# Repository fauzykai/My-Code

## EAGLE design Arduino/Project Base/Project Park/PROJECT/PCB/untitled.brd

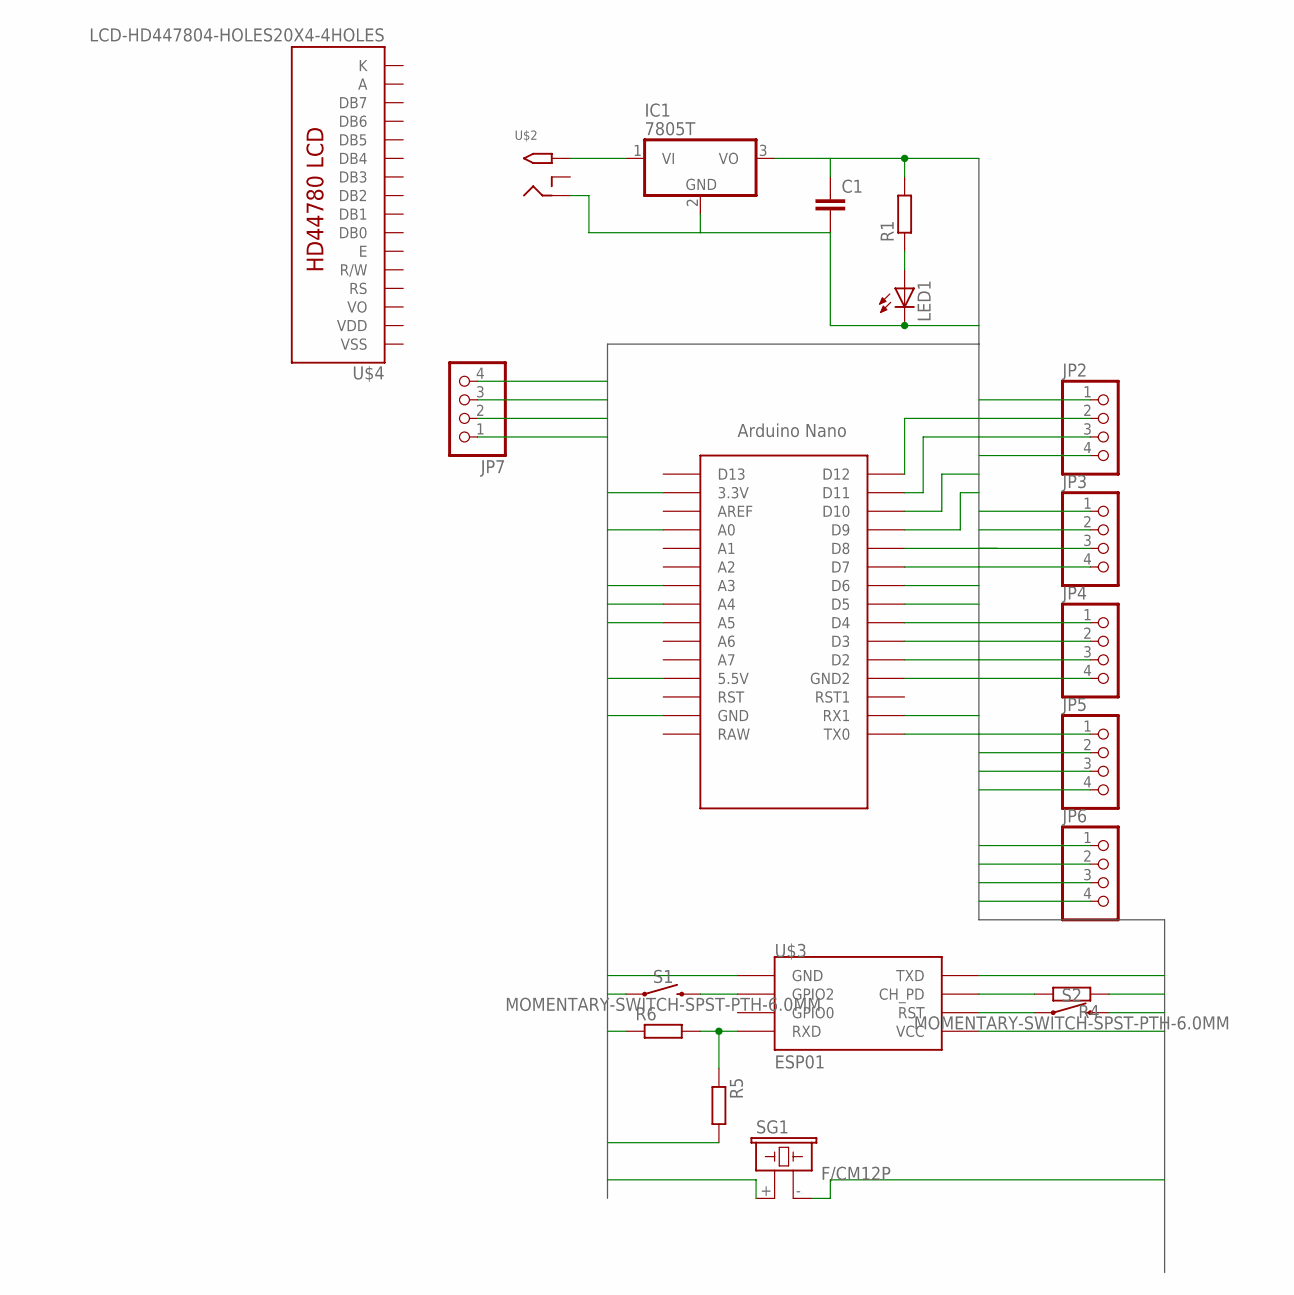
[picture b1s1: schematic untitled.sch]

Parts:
C1: C-EU025-030X050; C025-030X050
IC1: 7805T; TO220H
JP2, JP3, JP4, JP5, JP6, JP7: PINHD-1X4; 1X04
LED1: LED5MM
R1, R4, R5, R6: R-EU_0204/7; 0204/7
S1, S2: MOMENTARY-SWITCH-SPST-PTH-6.0MM; TACTILE_SWITCH_PTH_6.0MM
SG1: F/CM12P
U$1: NANO
U$2: 2.1MMJACKTHM; PJ-102A
U$3: ESP01
U$4: LCD-HD447804-HOLES20X4-4HOLES; LCD-20X4-4HOLES

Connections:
3V: R4.1, U$1.3.3V, U$3.VCC
A: U$4.P$15 (A)
BUZZ: SG1.+ (1), U$1.A3
E1: JP2.3, U$1.D11
E2: JP3.3, U$1.D9
E3: JP4.3, U$1.D7
E4: JP5.3, U$1.D5
E5: JP6.3, U$1.A0
GND: C1.2, IC1.2 (GND), JP2.4, JP3.4, JP4.4, JP5.4, JP6.4, JP7.1, LED1.K (C), R5.2, S1.1, S2.3 (2), SG1.- (2), U$1.GND, U$1.GND1 (GND2), U$2.RING, U$3.GND
K: U$4.P$16 (K)
unnamed: IC1.1 (VI), U$2.TIP
unnamed: R4.2, U$3.CH_PD
unnamed: R5.1, R6.2, U$3.RX (RXD)
unnamed: LED1.A, R1.1
unnamed: S1.3 (2), U$3.GPIO2
unnamed: S2.1, U$3.RST
RX: U$1.RX1
RXS: U$1.D3, U$3.TX (TXD)
SCL: JP7.3, U$1.A5
SDA: JP7.2, U$1.A4
T1: JP2.2, U$1.D12
T2: JP3.2, U$1.D10
T3: JP4.2, U$1.D8
T4: JP5.2, U$1.D6
T5: JP6.2, U$1.D4
TX: U$1.TX0
TXS: R6.1, U$1.D2
VCC: C1.1, IC1.3 (VO), JP2.1, JP3.1, JP4.1, JP5.1, JP6.1, JP7.4, R1.2, U$1.5V (5.5V)
VDD: U$4.P$2 (VDD)
VSS: U$4.P$1 (VSS)

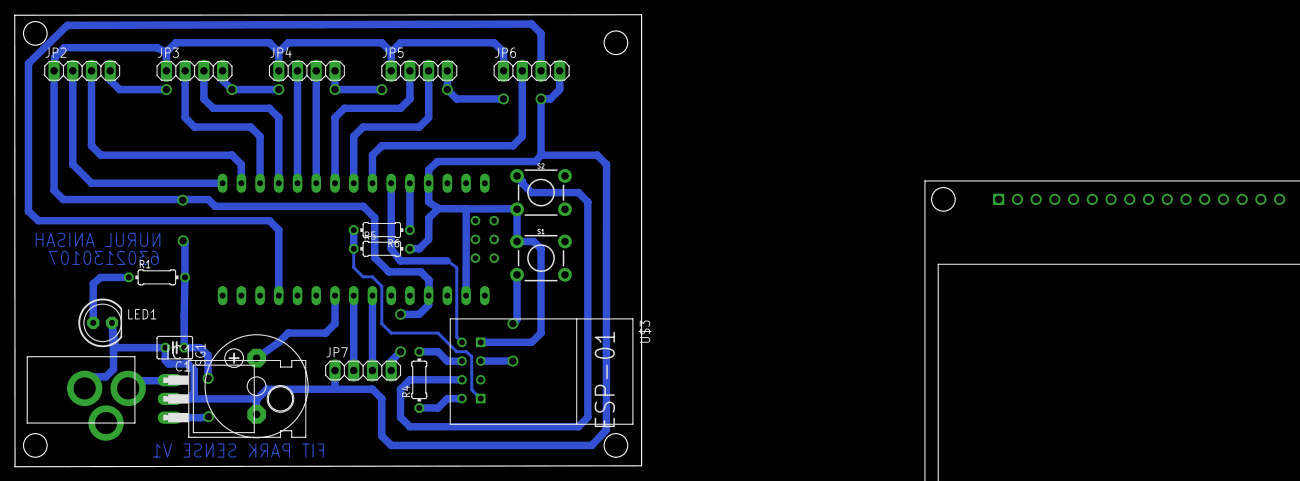
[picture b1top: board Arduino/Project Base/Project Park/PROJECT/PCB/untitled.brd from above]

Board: 2 copper layers, 85.0 x 61.3 mm, 20 parts (0 on the bottom side), 24 nets.

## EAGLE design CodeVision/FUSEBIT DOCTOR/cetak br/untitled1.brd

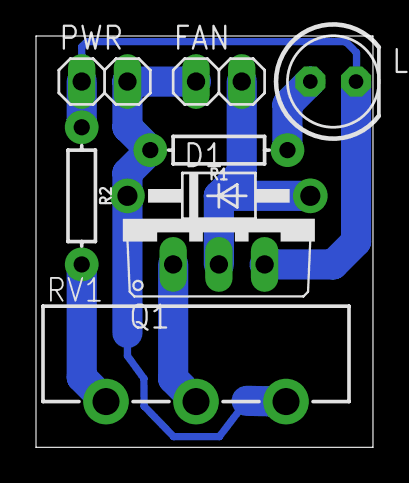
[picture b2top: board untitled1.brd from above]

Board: 2 copper layers, 18.7 x 22.9 mm, 8 parts (0 on the bottom side), 6 nets.

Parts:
D1: 1N4004; DO41-10
FAN: 1X02
LED1: LED5MM
PWR: 1X02
Q1: TO220V
R1, R2: 10M; AXIAL-0.3
RV1: POT_ALPHA_RV16AF-20

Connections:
GND: LED1.K, PWR.1, Q1.3, R2.P$1
unnamed: R2.P$2, RV1.1
unnamed: D1.A, FAN.2, Q1.2
unnamed: LED1.A, R1.P$1
unnamed: Q1.1, RV1.2
VCC: D1.C, FAN.1, PWR.2, R1.P$2, RV1.3

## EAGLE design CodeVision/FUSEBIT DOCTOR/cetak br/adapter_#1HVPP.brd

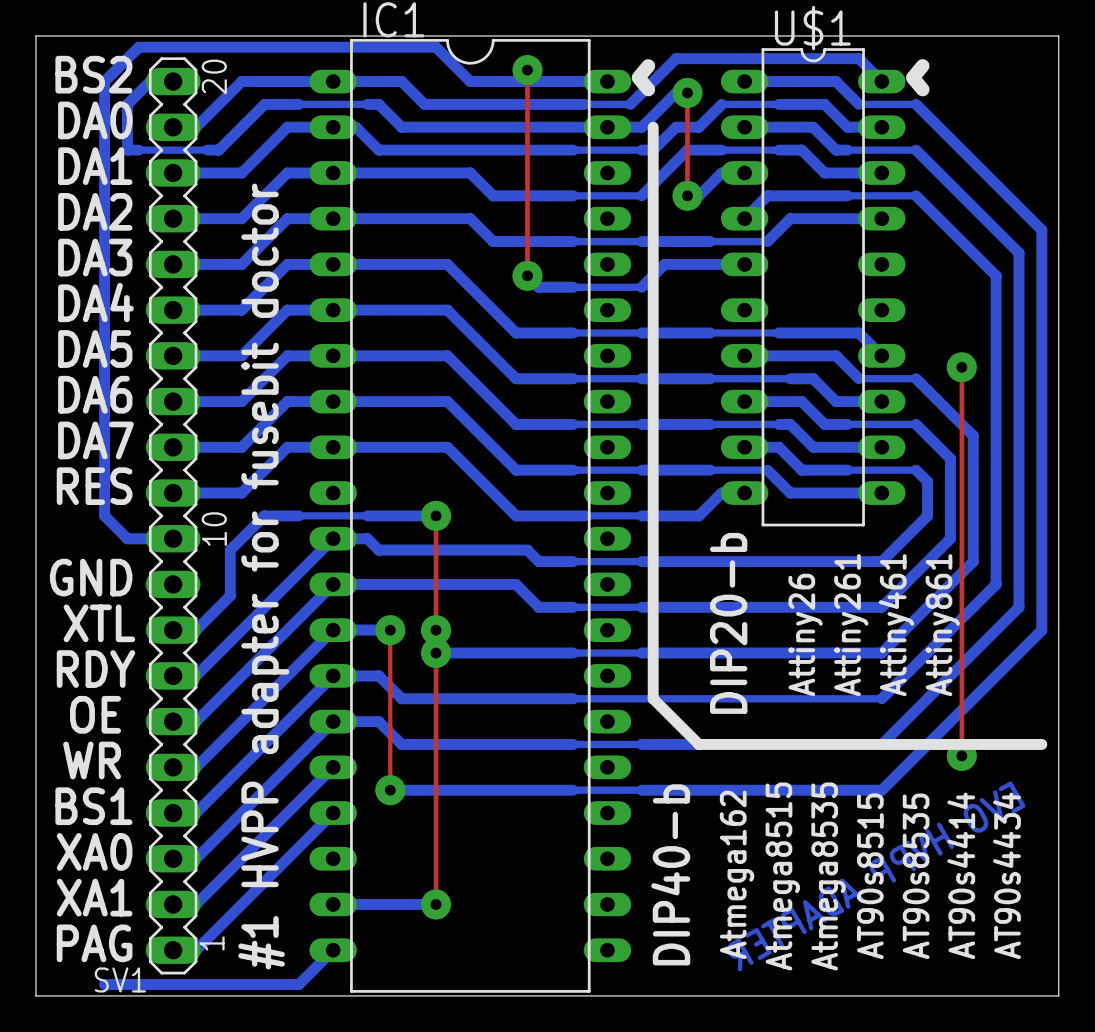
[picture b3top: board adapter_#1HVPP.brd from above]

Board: 2 copper layers, 56.8 x 53.3 mm, 3 parts (0 on the bottom side), 20 nets.

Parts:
IC1: AT90S8515P; DIL40
SV1: MA20-1
U$1: TINY26P; DIL20

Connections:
+5V: IC1.40, SV1.10, U$1.5
+12V: IC1.9, SV1.11, U$1.10
BS1: IC1.14, SV1.4, U$1.4
BS2: IC1.39, SV1.20, U$1.3
DATA0: IC1.1, SV1.19, U$1.20
DATA1: IC1.2, SV1.18, U$1.19
DATA2: IC1.3, SV1.17, U$1.18
DATA3: IC1.4, SV1.16, U$1.17
DATA4: IC1.5, SV1.15, U$1.14
DATA5: IC1.6, SV1.14, U$1.13
DATA6: IC1.7, SV1.13, U$1.12
DATA7: IC1.8, SV1.12, U$1.11
GND: IC1.20, SV1.9, U$1.16
OE: IC1.12, SV1.6, U$1.8
PAG: IC1.17, SV1.1
RDY: IC1.11, SV1.7, U$1.9
WR: IC1.13, SV1.5, U$1.1
XA0: IC1.15, SV1.3, U$1.2
XA1: IC1.16, SV1.2
XTAL1: IC1.19, SV1.8, U$1.7

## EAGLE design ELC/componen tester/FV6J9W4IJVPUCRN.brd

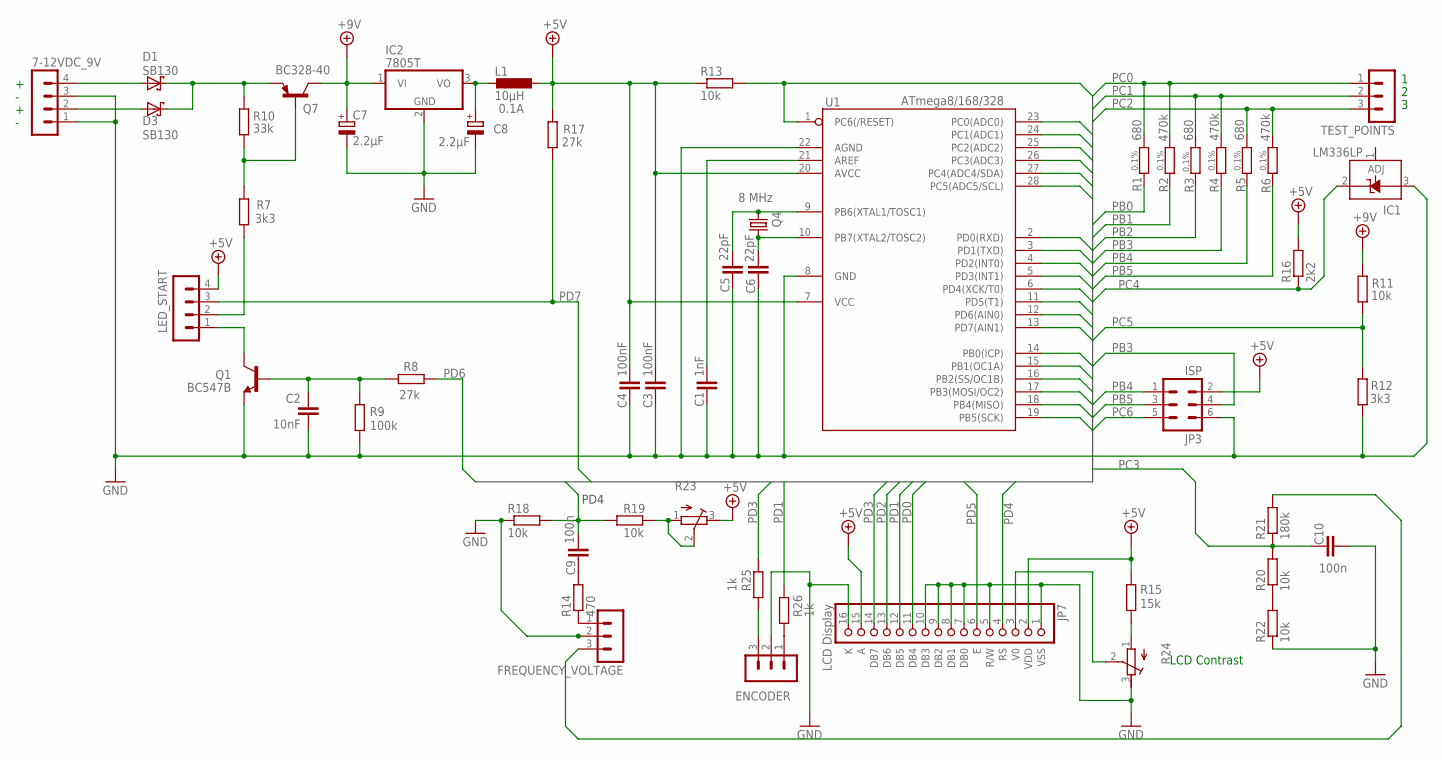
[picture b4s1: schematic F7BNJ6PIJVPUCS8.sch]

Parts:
7-12VDC_9V: MA04-1
C1: 1nF; C2.5-2
C2: 10nF; C2.5-3
C3, C4: 100nF; C025-025X050
C5, C6: 22pF; C2.5-3
C7, C8: 2.2µF; E5-5
C9, C10: 100n; C2.5-3
D1, D3: SB130; DIODE-3-5A-V
ENCODER: MA03-1
FREQUENCY_VOLTAGE: MA03-1
IC1: LM336LP; TO92
IC2: 7805T; TO220H
JP3: ISP; ML6
JP7: LCD Display; PINHD-1X16
L1: 10µH; 0204/7
LED_START: MA04-1
Q1: BC547B; TO92
Q4: 8 MHz; HC49/S
Q7: BC328-40; TO92-EBC
R1, R5: 680; 0207/10; TOLERANCE 0.1%
R2, R4, R6: 470k; 0207/10; TOLERANCE 0.1%
R3: 680; 0207/10; TOLERANCE 0,1%
R7: 3k3; 0207/10
R8: 27k; 0204/7
R9: 100k; 0204/7
R10: 33k; 0207/2V
R11, R13, R18, R19, R20, R22: 10k; 0207/10
R12: 3k3; 0207/2V
R14: 470; 0207/10
R15: 15k; 0207/10
R16: 2k2; 0204/5
R17: 27k; 0207/7
R21: 180k; 0207/10
R23, R24: R-TRIMM3339P; RTRIM3339P
R25: 1k; 0204/7
R26: 1k; 0207/10
TEST_POINTS: MA03-1
U1: ATmega8/168/328; DIL28-3

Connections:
+5V: C3.2, C4.1, JP3.2, JP7.2 (VDD), JP7.15 (A), L1.1, LED_START.4, R13.1, R15.1, R16.2, R17.2, R23.3 (E), U1.7 (VCC), U1.20 (AVCC)
+9V: C7.+, IC2.1 (VI), Q7.C, R11.1
GND: 7-12VDC_9V.1, 7-12VDC_9V.3, C1.1, C2.2, C3.1, C4.2, C5.1, C6.1, C7.-, C8.-, C10.1, ENCODER.2, FREQUENCY_VOLTAGE.2, IC1.3 (A), IC2.2 (GND), JP3.6, JP7.1 (VSS), JP7.5 (R/W), JP7.7 (DB0), JP7.8 (DB1), JP7.9 (DB2), JP7.10 (DB3), JP7.16 (K), Q1.1 (E), R9.1, R12.1, R18.1, R22.1, R24.3 (E), U1.8 (GND), U1.22 (AGND)
unnamed: R15.2, R24.1 (A)
unnamed: JP7.3 (V0), R24.2 (S)
unnamed: FREQUENCY_VOLTAGE.1, R14.1
unnamed: C9.1, R14.2
unnamed: D1.C, D3.C, Q7.E, R10.1
unnamed: R19.2, R23.1 (A), R23.2 (S)
unnamed: R20.1, R22.2
unnamed: LED_START.1, Q1.3 (C)
unnamed: 7-12VDC_9V.4, D1.A
unnamed: C1.2, U1.21 (AREF)
unnamed: ENCODER.3, R25.1
unnamed: C5.2, Q4.2, U1.9 (PB6(XTAL1/TOSC1))
unnamed: C6.2, Q4.1, U1.10 (PB7(XTAL2/TOSC2))
unnamed: ENCODER.1, R26.1
unnamed: FREQUENCY_VOLTAGE.3, R21.2
unnamed: C8.+, IC2.3 (VO), L1.2
unnamed: 7-12VDC_9V.2, D3.A
unnamed: Q7.B, R7.2, R10.2
unnamed: C2.1, Q1.2 (B), R8.2, R9.2
PB0: R1.1, U1.14 (PB0(ICP))
PB1: R2.1, U1.15 (PB1(OC1A))
PB2: R3.1, U1.16 (PB2(SS/OC1B))
PB3: JP3.4, R4.1, U1.17 (PB3(MOSI/OC2))
PB4: JP3.1, R5.1, U1.18 (PB4(MISO))
PB5: JP3.3, R6.1, U1.19 (PB5(SCK))
PC0: R1.2, R2.2, TEST_POINTS.1, U1.23 (PC0(ADC0))
PC1: R3.2, R4.2, TEST_POINTS.2, U1.24 (PC1(ADC1))
PC2: R5.2, R6.2, TEST_POINTS.3, U1.25 (PC2(ADC2))
PC3: C10.2, R20.2, R21.1, U1.26 (PC3(ADC3))
PC4: IC1.2 (C), R16.1, U1.27 (PC4(ADC4/SDA))
PC5: R11.2, R12.2, U1.28 (PC5(ADC5/SCL))
PC6: JP3.5, R13.2, U1.1 (PC6(/RESET))
PD0: JP7.11 (DB4), U1.2 (PD0(RXD))
PD1: JP7.12 (DB5), R26.2, U1.3 (PD1(TXD))
PD2: JP7.13 (DB6), U1.4 (PD2(INT0))
PD3: JP7.14 (DB7), R25.2, U1.5 (PD3(INT1))
PD4: C9.2, JP7.4 (RS), R18.2, R19.1, U1.6 (PD4(XCK/T0))
PD5: JP7.6 (E), U1.11 (PD5(T1))
PD6: R8.1, U1.12 (PD6(AIN0))
PD7: LED_START.3, R17.1, U1.13 (PD7(AIN1))
START: LED_START.2, R7.1

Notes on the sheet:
LCD Contrast
PC4
PD4
PC3

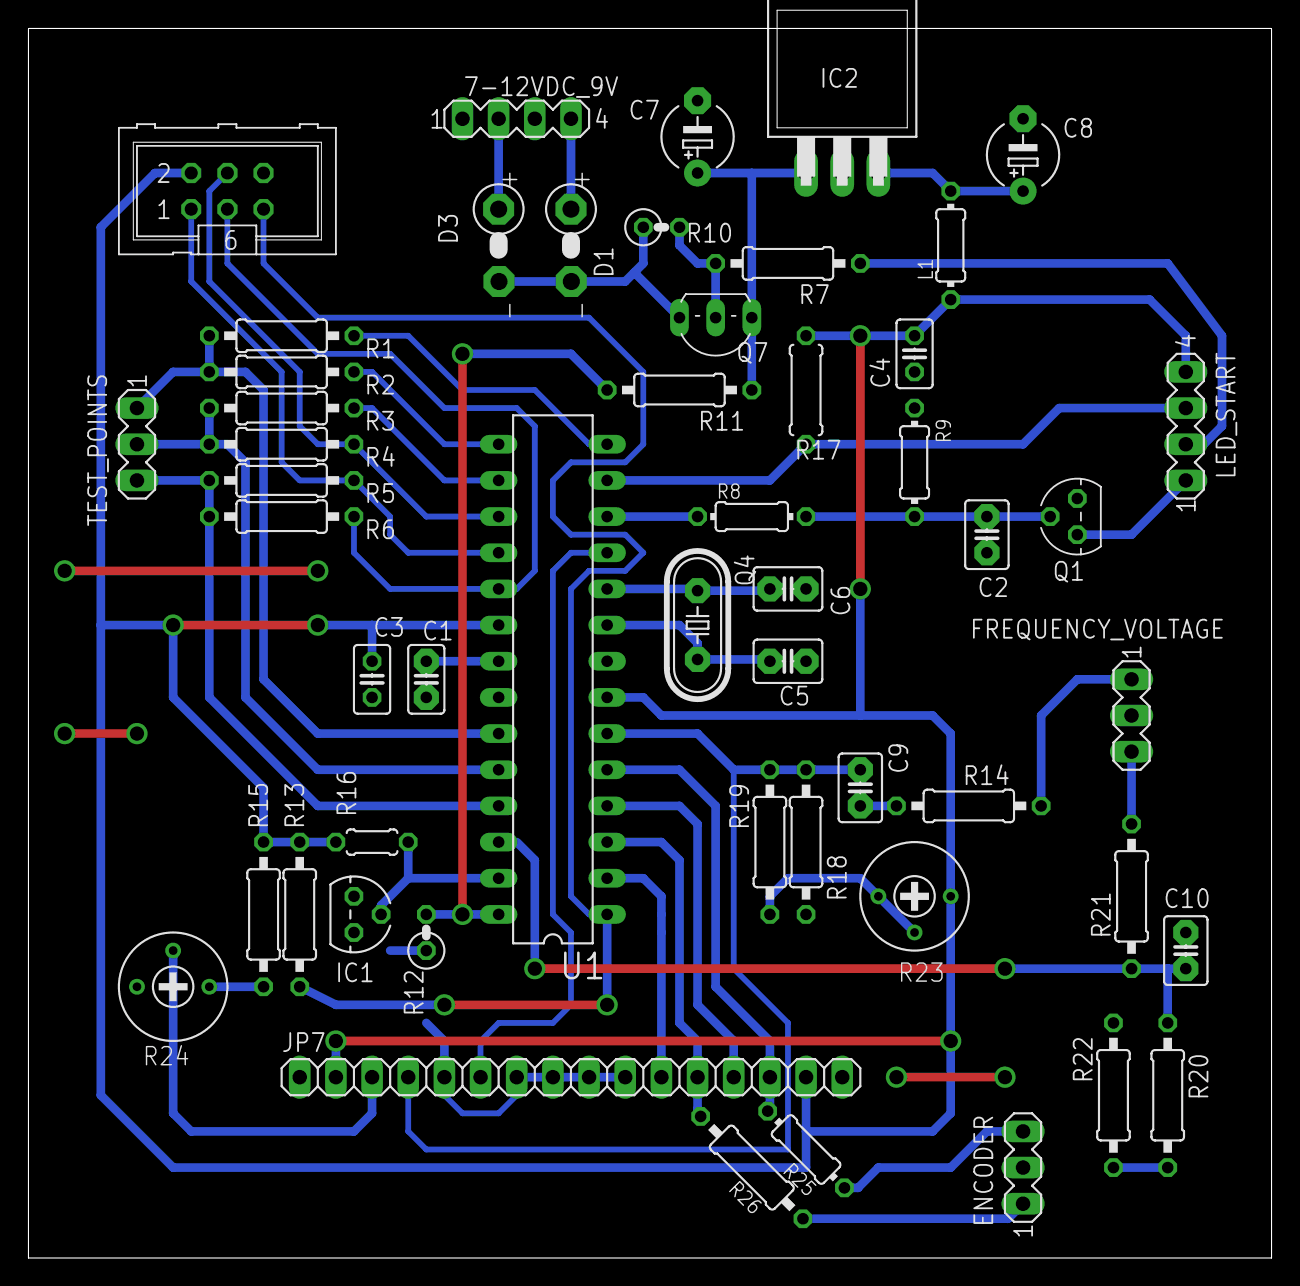
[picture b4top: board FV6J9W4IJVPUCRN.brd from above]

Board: 2 copper layers, 87.3 x 86.3 mm, 52 parts (0 on the bottom side), 44 nets.

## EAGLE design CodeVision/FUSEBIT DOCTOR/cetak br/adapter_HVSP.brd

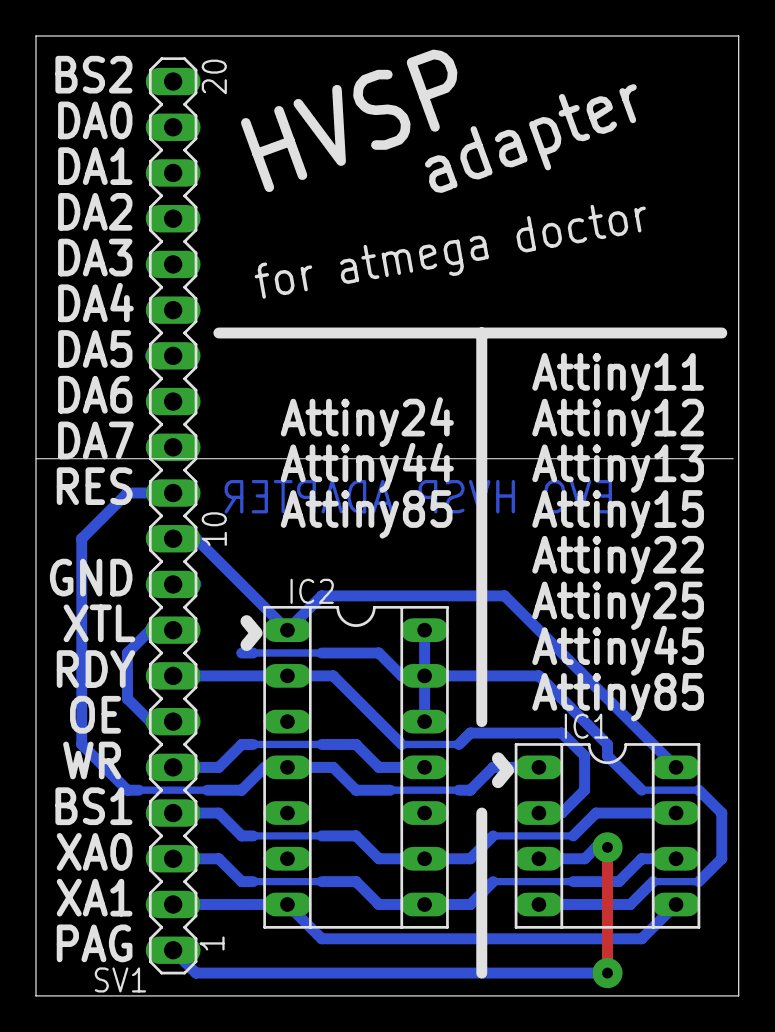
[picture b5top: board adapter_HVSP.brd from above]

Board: 2 copper layers, 39.0 x 53.3 mm, 3 parts (0 on the bottom side), 10 nets.

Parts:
IC1: SOCKED-08
IC2: SOCKED-14
SV1: MA20-1

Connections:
+5V: IC1.8, IC2.1, SV1.10
+12V: IC1.1, IC2.4, SV1.11
BS1: IC1.7, IC2.9, SV1.4
GND: IC1.4, IC2.12, IC2.13, IC2.14, SV1.9
PAG: IC1.3, SV1.1
RDY: IC1.2, IC2.2, SV1.7
WR: IC2.11, SV1.5
XA0: IC1.6, IC2.8, SV1.3
XA1: IC1.5, IC2.7, SV1.2
XTAL1/OE: SV1.6, SV1.8

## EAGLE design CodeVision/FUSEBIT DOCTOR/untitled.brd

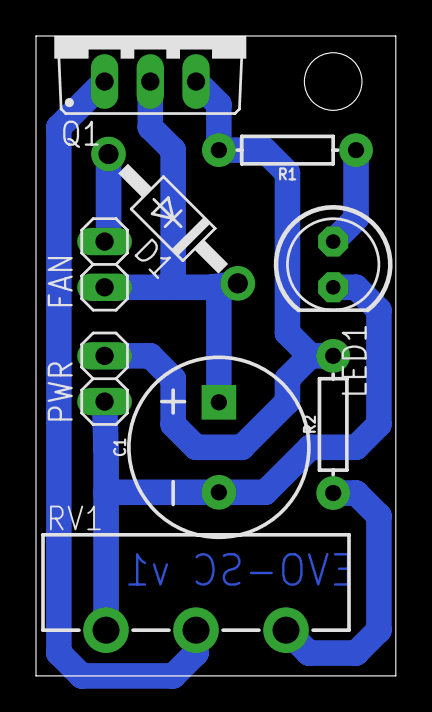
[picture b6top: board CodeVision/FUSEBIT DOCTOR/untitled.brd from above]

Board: 2 copper layers, 20.0 x 35.5 mm, 9 parts (0 on the bottom side), 6 nets.

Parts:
C1: 1mF; CPOL-RADIAL-5MM-10MM
D1: 1N4004; DO41-10
FAN: 1X02
LED1: LED5MM
PWR: 1X02
Q1: IRF9530; TO220BV
R1, R2: 10M; AXIAL-0.3
RV1: POT_ALPHA_RV16AF-20

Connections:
GND: C1.-, D1.A, FAN.2, LED1.K, PWR.1, RV1.1
unnamed: R2.P$1, RV1.3
unnamed: LED1.A, R1.P$1
unnamed: Q1.G, RV1.2
unnamed: C1.+, D1.C, FAN.1, Q1.D
VCC: PWR.2, Q1.S, R1.P$2, R2.P$2

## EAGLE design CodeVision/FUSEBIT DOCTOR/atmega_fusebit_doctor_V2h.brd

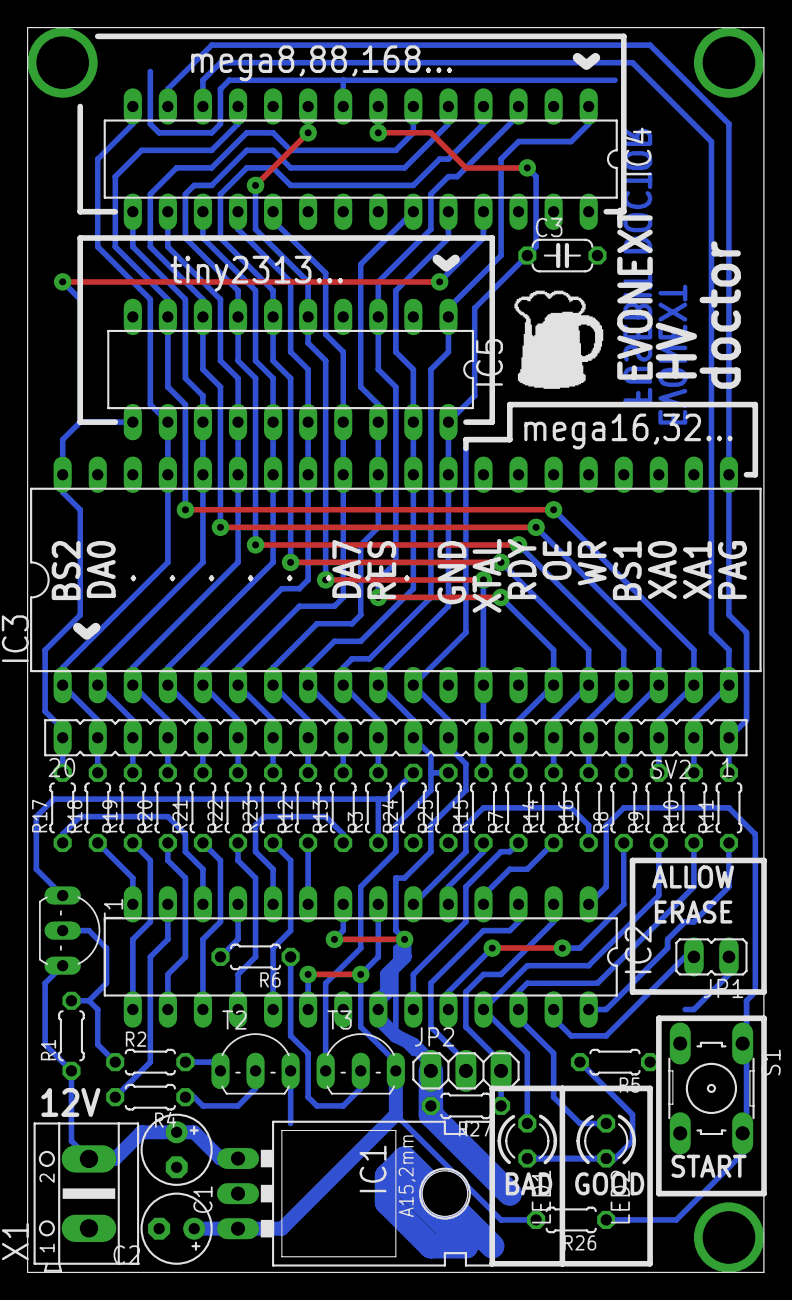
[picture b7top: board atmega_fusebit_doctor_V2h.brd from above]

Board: 2 copper layers, 53.3 x 90.2 mm, 45 parts (0 on the bottom side), 51 nets.

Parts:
C1: 100uF; E2,5-5
C2: 10uF; E2,5-5
C3: 10nF; C050-024X044
IC1: 7805; 78XXL
IC2: ATMEGA8-DOC; DIL28-3
IC3: MEGA16/32/644...; DIL40
IC4: MEGA8/88/168...; DIL28-3
IC5: AT90S2313/TINY2313; DIL20
JP1: ERASE; JP1
JP2: RS232; 1X03
LED1: red; LED3MM
LED2: green; LED3MM
R1, R27: 10K; 0204/5
R2, R7, R8, R9, R10, R11, R12, R13, R14, R15, R16, R17, R18, R19, R20, R21, R22, R23, R24, R26: 1K; 0204/5
R3, R25: 100; 0204/5
R4, R6: 4K7; 0204/5
R5: 330; 0204/5
S1: START; B3F-10XX
SV2: FE20
T1, T3: BC557; TO92-EBC
T2: BC547; TO92-EBC
X1: AK500/2

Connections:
+5V: C3.1, IC3.10, IC4.7, IC5.20, R25.2, SV2.10, T3.C
+12V: IC3.9, IC4.1, IC5.1, R3.2, SV2.11
BS1: IC3.18, IC4.6, IC5.8, R8.2, SV2.4
BS2: IC3.40, IC4.25, IC5.11, R17.2, SV2.20
DATA0: IC3.1, IC4.14, IC5.12, R18.2, SV2.19
DATA1: IC3.2, IC4.15, IC5.13, R19.2, SV2.18
DATA2: IC3.3, IC4.16, IC5.14, R20.2, SV2.17
DATA3: IC3.4, IC4.17, IC5.15, R21.2, SV2.16
DATA4: IC3.5, IC4.18, IC5.16, R22.2, SV2.15
DATA5: IC3.6, IC4.19, IC5.17, R23.2, SV2.14
DATA6: IC3.7, IC4.23, IC5.18, R12.2, SV2.13
DATA7: IC3.8, IC4.24, IC5.19, R13.2, SV2.12
GND: C1.-, C2.-, C3.2, IC1.GND, IC2.8, IC2.22, IC3.11, IC4.8, IC5.10, JP1.1, JP2.1, R5.1, R24.1, R25.1, R27.2, S1.3, S1.4, SV2.9, T2.E, X1.1
unnamed: R6.1, T3.B
unnamed: IC2.14, R18.1
unnamed: IC2.3, JP2.2
unnamed: IC2.28, R11.1
unnamed: IC2.6, R16.1
unnamed: IC2.4, R14.1
unnamed: IC2.2, JP2.3, R27.1
unnamed: R2.2, T2.C
unnamed: IC2.9, R12.1
unnamed: IC2.10, R13.1
unnamed: IC2.13, R4.2
unnamed: IC2.11, R6.2
unnamed: IC2.15, R19.1
unnamed: IC2.16, R20.1
unnamed: IC2.5, R15.1
unnamed: IC2.23, R7.1
unnamed: R3.1, R24.2, T1.C
unnamed: IC2.17, R21.1
unnamed: IC2.18, R22.1
unnamed: IC2.19, R23.1
unnamed: IC2.12, R17.1
unnamed: R4.1, T2.B
unnamed: IC2.27, JP1.2
unnamed: LED1.K, LED2.K, R5.2
unnamed: R1.2, R2.1, T1.B
unnamed: IC2.24, R8.1
unnamed: IC2.1, R26.1, S1.1, S1.2
unnamed: IC2.26, LED2.A, R10.1
unnamed: IC2.25, LED1.A, R9.1
OE: IC3.16, IC4.4, IC5.6, R14.2, SV2.6
PAG: IC3.21, IC4.13, R11.2, SV2.1
RDY: IC3.15, IC4.3, IC5.3, R7.2, SV2.7
V+: C1.+, IC1.IN, R1.1, T1.E, X1.2
VCC: C2.+, IC1.OUT, IC2.7, IC2.20, R26.2, T3.E
WR: IC3.17, IC4.5, IC5.7, R16.2, SV2.5
XA0: IC3.19, IC4.11, IC5.9, R9.2, SV2.3
XA1: IC3.20, IC4.12, R10.2, SV2.2
XTAL1: IC3.13, IC4.9, IC5.5, R15.2, SV2.8

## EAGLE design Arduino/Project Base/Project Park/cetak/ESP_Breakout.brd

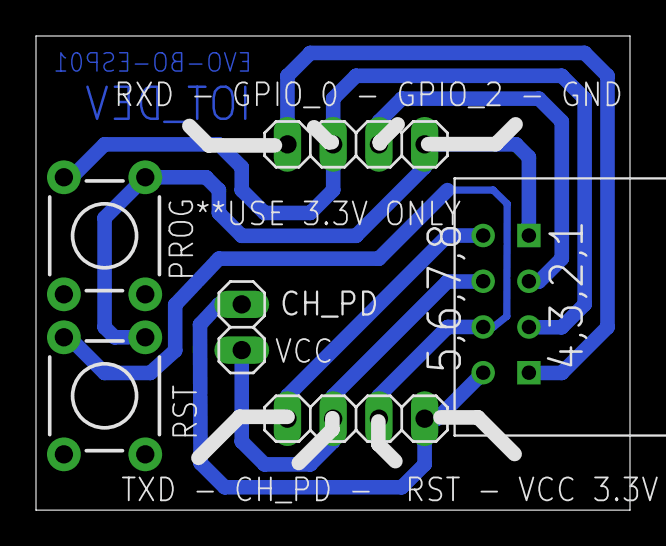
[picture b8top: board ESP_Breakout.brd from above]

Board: 2 copper layers, 33.0 x 26.3 mm, 6 parts (0 on the bottom side), 8 nets.

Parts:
CH_PD: 1X02
JP1, JP2: 1X04
S1: PROG; TACTILE_SWITCH_PTH_6.0MM
S2: RST; TACTILE_SWITCH_PTH_6.0MM
U$1: ESP01_BREAKOUT; ESP01

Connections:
unnamed: JP1.4, S1.1, S2.1, U$1.GND
unnamed: JP1.3, U$1.GPIO2
unnamed: JP1.2, S1.3, U$1.GPIO0
unnamed: JP1.1, U$1.RX
unnamed: JP2.1, U$1.TX
unnamed: CH_PD.2, JP2.2, U$1.CH_PD
unnamed: JP2.3, S2.3, U$1.RST
unnamed: CH_PD.1, JP2.4, U$1.VCC

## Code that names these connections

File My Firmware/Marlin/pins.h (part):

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#define TEMP_2_PIN         -1

#define SDPOWER            -1
#define SDSS               20  // PB0 - 8 in marlin env.
#define LED_PIN            -1
#define PS_ON_PIN          -1
#define KILL_PIN           -1
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*                        ATMega644
*
*                        +---\/---+
*            (D 0) PB0  1|        |40  PA0 (AI 0 / D31)
*            (D 1) PB1  2|        |39  PA1 (AI 1 / D30)
*       INT2 (D 2) PB2  3|        |38  PA2 (AI 2 / D29)
*        PWM (D 3) PB3  4|        |37  PA3 (AI 3 / D28)
*        PWM (D 4) PB4  5|        |36  PA4 (AI 4 / D27)
*       MOSI (D 5) PB5  6|        |35  PA5 (AI 5 / D26)
*       MISO (D 6) PB6  7|        |34  PA6 (AI 6 / D25)
*        SCK (D 7) PB7  8|        |33  PA7 (AI 7 / D24)
*                  RST  9|        |32  AREF
*                  VCC 10|        |31  GND
*                  GND 11|        |30  AVCC
*                XTAL2 12|        |29  PC7 (D 23)
*                XTAL1 13|        |28  PC6 (D 22)
*       RX0 (D 8)  PD0 14|        |27  PC5 (D 21) TDI
*       TX0 (D 9)  PD1 15|        |26  PC4 (D 20) TDO
*  INT0 RX1 (D 10) PD2 16|        |25  PC3 (D 19) TMS
*  INT1 TX1 (D 11) PD3 17|        |24  PC2 (D 18) TCK
*       PWM (D 12) PD4 18|        |23  PC1 (D 17) SDA
*       PWM (D 13) PD5 19|        |22  PC0 (D 16) SCL
*       PWM (D 14) PD6 20|        |21  PD7 (D 15) PWM
*                        +--------+
*
****************************************************************************************/
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
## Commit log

2019-03-10 more

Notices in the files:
parts and their libraries:
SparkFun-Switches: Licensing: Creative Commons ShareAlike 4.0 International - https://creativecommons.org/licenses/by-sa/4.0
